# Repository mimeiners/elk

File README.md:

# HSB Fak. 4 ET B.Eng. M 5.3 Elektronik (ELK)

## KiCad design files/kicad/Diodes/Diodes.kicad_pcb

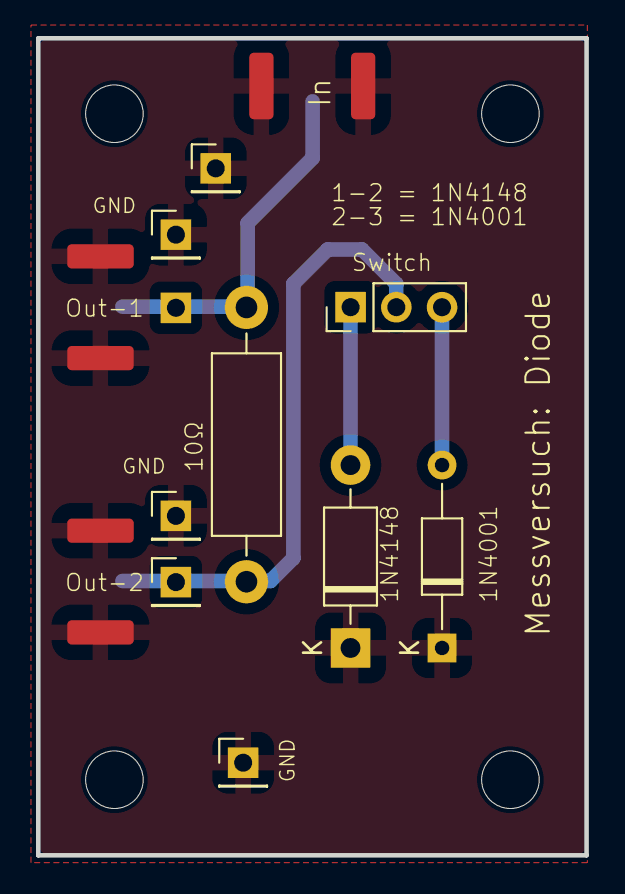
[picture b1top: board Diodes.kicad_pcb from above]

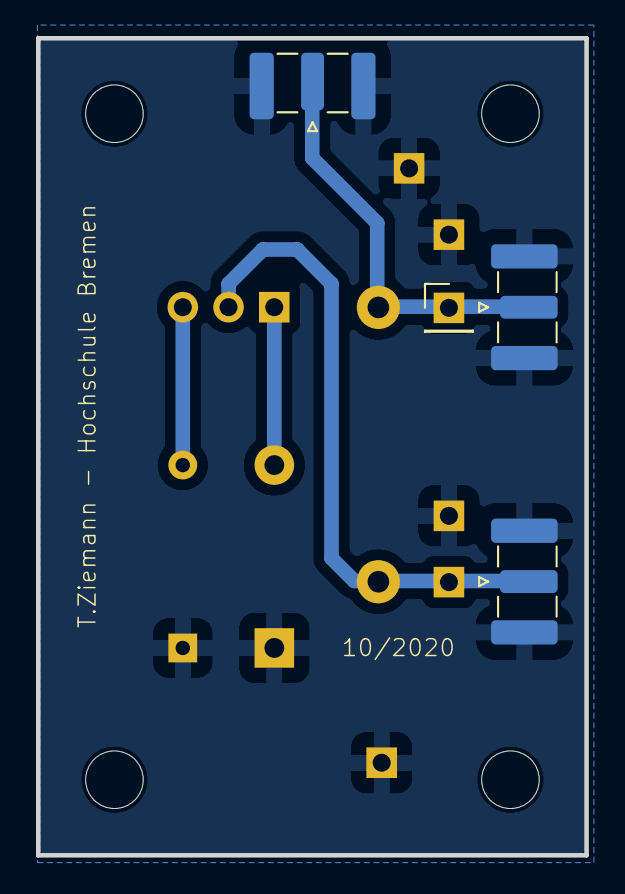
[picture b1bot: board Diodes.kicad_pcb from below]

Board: 2 copper layers, 30.5 x 45.4 mm, 17 parts (4 on the bottom side), 5 nets.

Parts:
D1: 1N4148; D_DO-35_SOD27_P10.16mm_Horizontal
D2: 1N4001; D_DO-41_SOD81_P10.16mm_Horizontal
GND1, GND2, GND3, GND4: Conn_01x01_Pin; PinHeader_1x01_P2.54mm_Vertical
H1, H2, H3, H4: MountingHole; MountingHole_3.2mm_M3
IN2: Conn_Coaxial; SMA_Samtec_SMA-J-P-H-ST-EM1_EdgeMount
Jumper1: Jumper_3_Bridged12; PinHeader_1x03_P2.54mm_Vertical
OUT-1, OUT-3: Conn_01x01_Pin; PinHeader_1x01_P2.54mm_Vertical
OUT-2, OUT-4: Conn_Coaxial; SMA_Samtec_SMA-J-P-H-ST-EM1_EdgeMount
R1: 10 Ohm; R_Axial_DIN0411_L9.9mm_D3.6mm_P15.24mm_Horizontal

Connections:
/In-1: IN2.1 (In), OUT-1.1, OUT-2.1 (In), R1.1
/Out-2: Jumper1.2 (C), OUT-3.1, OUT-4.1 (In), R1.2
GND: D1.1 (K), D2.1 (K), GND1.1, GND2.1, GND3.1, GND4.1, IN2.2 (Ext), OUT-2.2 (Ext), OUT-4.2 (Ext)
unnamed: D1.2 (A), Jumper1.3 (B)
unnamed: D2.2 (A), Jumper1.1 (A)

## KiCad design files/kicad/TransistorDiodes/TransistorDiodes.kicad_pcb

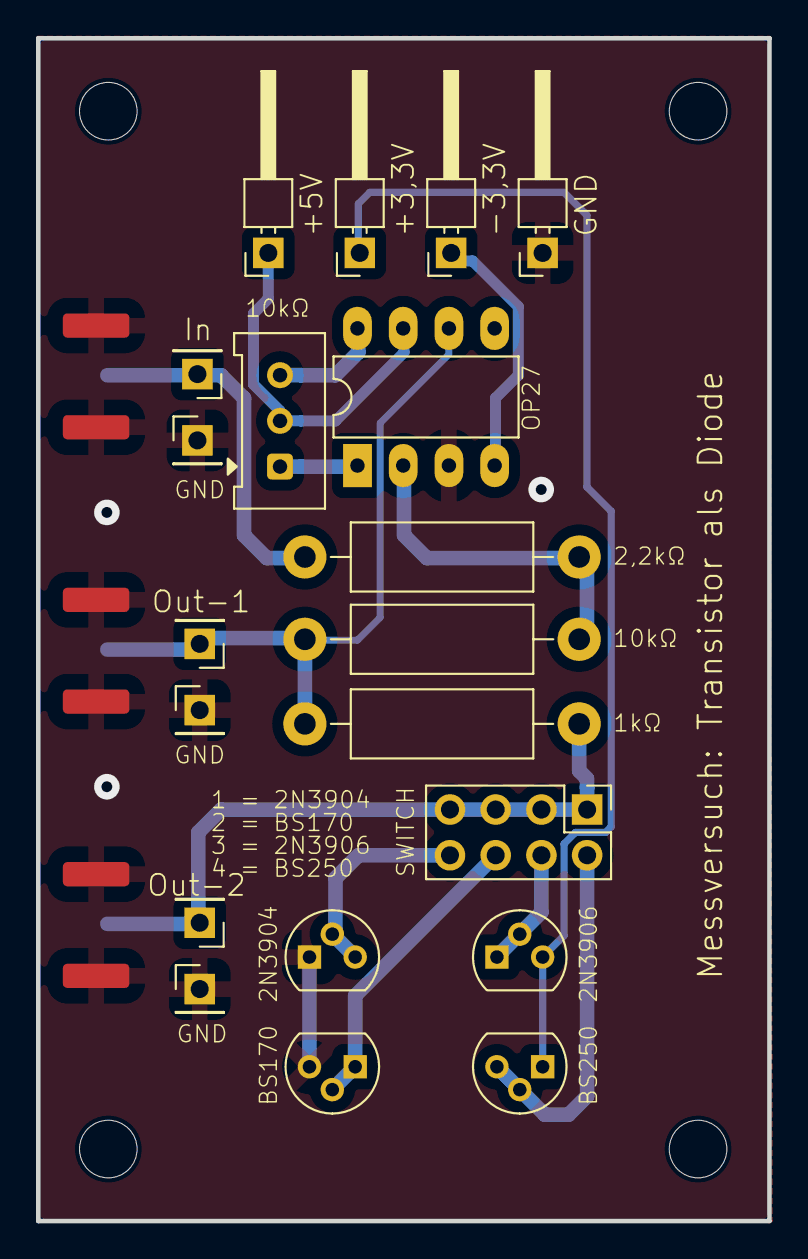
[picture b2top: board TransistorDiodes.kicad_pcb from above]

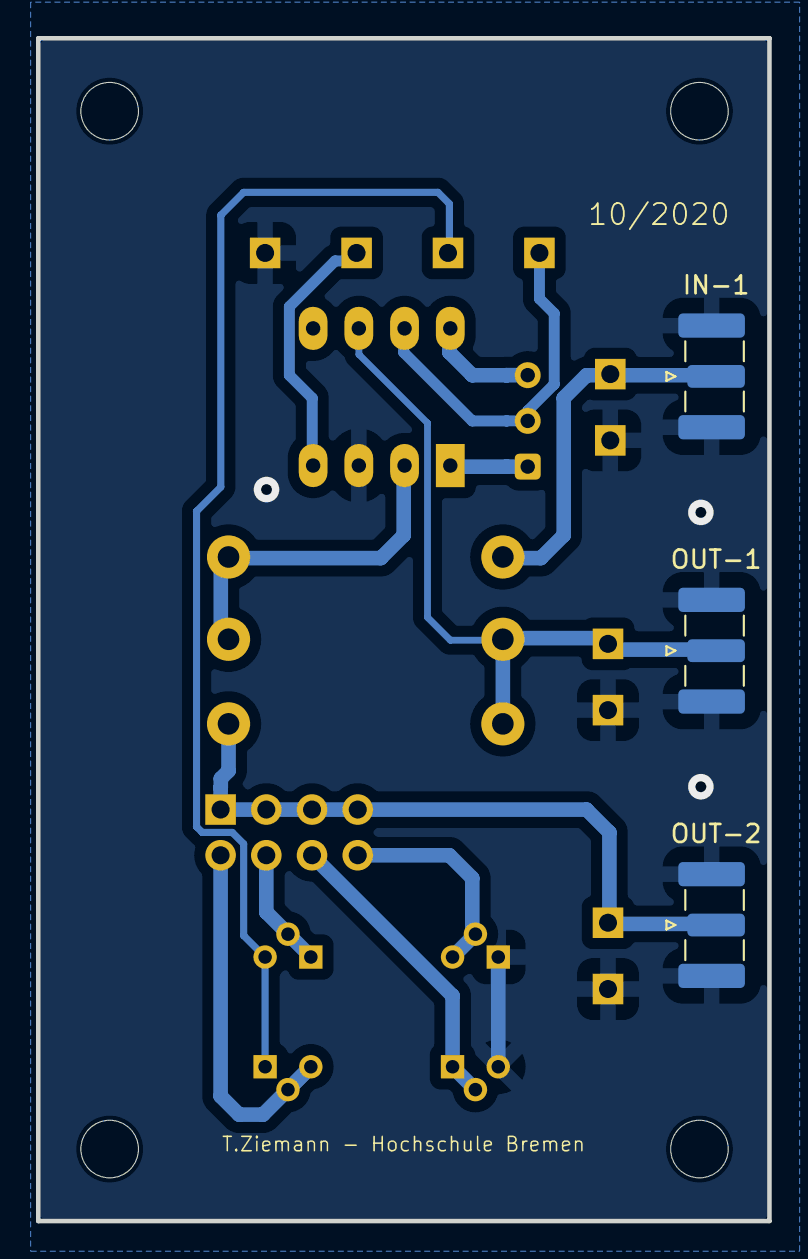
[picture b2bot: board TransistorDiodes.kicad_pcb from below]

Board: 2 copper layers, 40.6 x 65.7 mm, 27 parts (3 on the bottom side), 14 nets.

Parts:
+2: Conn_01x01_Pin; PinHeader_1x01_P2.54mm_Horizontal
-1: Conn_01x01_Pin; PinHeader_1x01_P2.54mm_Horizontal
GND1, GND2, GND3: Conn_01x01_Pin; PinHeader_1x01_P2.54mm_Vertical
H1, H2, H3, H4: MountingHole; MountingHole_3.2mm_M3
IN-1: Conn_Coaxial; SMA_Samtec_SMA-J-P-H-ST-EM1_EdgeMount
IN-2: Conn_01x01_Pin; PinHeader_1x01_P2.54mm_Vertical
J1: Conn_01x01_Pin; PinHeader_1x01_P2.54mm_Horizontal
JumperTransistorauswahl1: Conn_02x04_Odd_Even; PinHeader_2x04_P2.54mm_Vertical
OUT-1, OUT-2: Conn_Coaxial; SMA_Samtec_SMA-J-P-H-ST-EM1_EdgeMount
OUT-3, OUT-4: Conn_01x01_Pin; PinHeader_1x01_P2.54mm_Vertical
Q1: 2N3904; TO-92
Q2: 2N3906; TO-92
Q3: BS170; TO-92
Q4: BS250; TO-92
R1: 22k; R_Axial_DIN0411_L9.9mm_D3.6mm_P15.24mm_Horizontal
R2: 10k; R_Axial_DIN0411_L9.9mm_D3.6mm_P15.24mm_Horizontal
R3: 1k; R_Axial_DIN0411_L9.9mm_D3.6mm_P15.24mm_Horizontal
RV1: 10k; Potentiometer_Bourns_3386W_Horizontal
ST01: Conn_01x01_Pin; PinHeader_1x01_P2.54mm_Horizontal
U1: DIP-8_W7.62mm_LongPads

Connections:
+3V3: +2.1, Q2.3 (C), Q4.1 (D)
+5V: RV1.2, ST01.1, U1.7 (V+)
-3V3: -1.1, U1.4 (V-)
/2N3904: JumperTransistorauswahl1.8, Q1.2 (B), Q1.3 (C)
/2N3906: JumperTransistorauswahl1.6, Q3.1 (D), Q3.2 (G)
/BS170: JumperTransistorauswahl1.4, Q2.1 (E), Q2.2 (B)
/BS250: JumperTransistorauswahl1.2, Q4.2 (G), Q4.3 (S)
/IN-1: IN-1.1 (In), IN-2.1, R1.1
/OUT-1: OUT-1.1 (In), OUT-3.1, R2.2, R3.1, U1.6
/OUT-2: JumperTransistorauswahl1.1, JumperTransistorauswahl1.3, JumperTransistorauswahl1.5, JumperTransistorauswahl1.7, OUT-2.1 (In), OUT-4.1, R3.2
GND: GND1.1, GND2.1, GND3.1, IN-1.2 (Ext), J1.1, OUT-1.2 (Ext), OUT-2.2 (Ext), Q1.1 (E), Q3.3 (S), U1.3 (+)
unnamed: RV1.1, U1.1 (VOS)
unnamed: RV1.3, U1.8 (VOS)
unnamed: R1.2, R2.1, U1.2 (-)

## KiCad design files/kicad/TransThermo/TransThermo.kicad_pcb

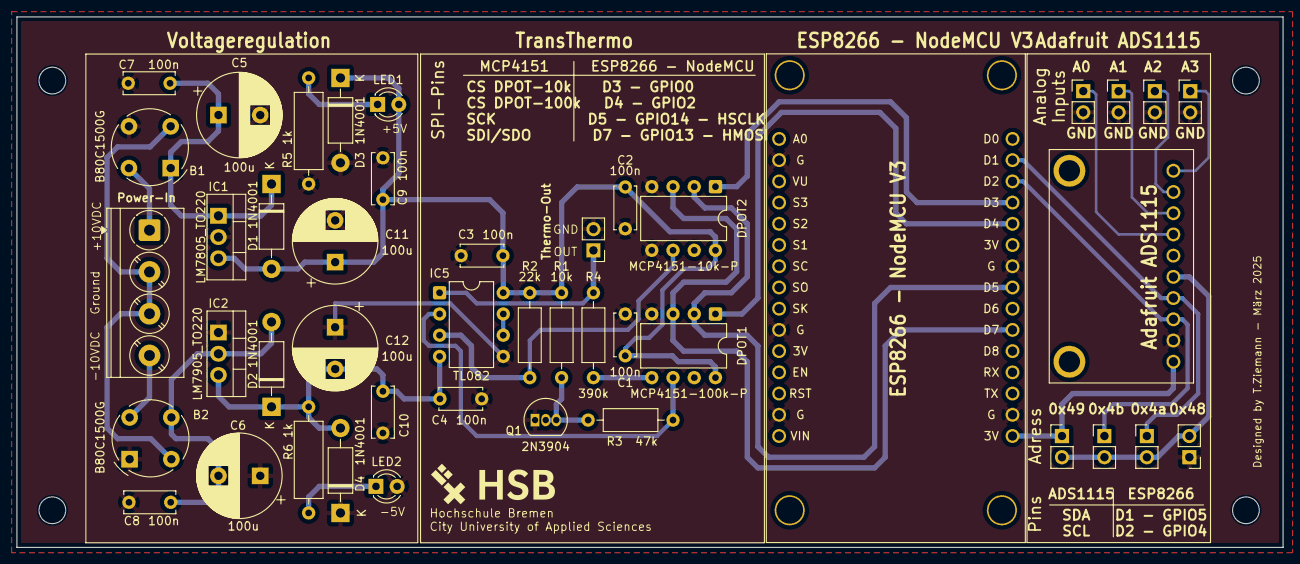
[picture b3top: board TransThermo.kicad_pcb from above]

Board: 2 copper layers, 151.6 x 63.5 mm, 49 parts (0 on the bottom side), 28 nets.

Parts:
B1, B2: B80C1500G; Diode_Bridge_Round_D9.0mm
C1, C2, C3, C4: 100n; C_Disc_D5.0mm_W2.5mm_P5.00mm
C5, C6, C11, C12: 100u; CP_Radial_D10.0mm_P5.00mm
C7, C8, C9, C10: 100n; C_Disc_D6.0mm_W2.5mm_P5.00mm
D1, D2, D3, D4: 1N4001; D_DO-41_SOD81_P10.16mm_Horizontal
DPOT1: MCP4151-100k-P; DIP-8_W7.62mm
DPOT2: MCP4151-10k-P; DIP-8_W7.62mm
G*: LOGO; HSB-Logo
H1, H2, H3, H4: MountingHole; MountingHole_3.2mm_M3
IC1: LM7805_TO220; TO-220-3_Vertical
IC2: LM7905_TO220; TO-220-3_Vertical
IC3: ESP8266 - NodeMCU V3; ESP8266-NodeMCU-V3
IC4: Adafruit-ADS1115
IC5: TL082; DIP-8_W7.62mm
J1: +/- Input (15V-25V); TerminalBlock_Phoenix_PT-1,5-4-5.0-H_1x04_P5.00mm_Horizontal
J2: Conn_01x02_Socket; PinHeader_1x02_P2.54mm_Vertical
JP1: Jumper_2_Bridged; PinHeader_1x02_P2.54mm_Vertical
JP2, JP3, JP4, JP5, JP6, JP7, JP8: Jumper_2_Open; PinHeader_1x02_P2.54mm_Vertical
LED1, LED2: LED; LED_D3.0mm
Q1: 2N3904; TO-92_Inline
R1: 10k; R_Axial_DIN0207_L6.3mm_D2.5mm_P10.16mm_Horizontal
R2: 22k; R_Axial_DIN0207_L6.3mm_D2.5mm_P10.16mm_Horizontal
R3: 47k; R_Axial_DIN0207_L6.3mm_D2.5mm_P10.16mm_Horizontal
R4: 390k; R_Axial_DIN0207_L6.3mm_D2.5mm_P10.16mm_Horizontal
R5, R6: 1k; R_Axial_DIN0309_L9.0mm_D3.2mm_P12.70mm_Horizontal

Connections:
0: B1.3 (-), B2.1 (+), C1.2, C2.2, C3.2, C4.1, C5.2, C6.1, C7.2, C8.1, C9.2, C10.1, C11.2, C12.1, D3.2 (A), D4.1 (K), DPOT1.4 (V_{SS}), DPOT2.4 (V_{SS}), DPOT2.5 (P0A), IC1.2 (GND), IC2.1 (GND), IC3.2 (G-GND), IC3.10 (G-GND), IC3.14 (G-GND), IC3.17 (G-GND), IC3.24 (G-GND), IC4.2 (GND), IC5.5 (+), J2.2, JP1.1 (A), JP5.2 (B), JP6.2 (B), JP7.2 (B), JP8.2 (B), LED2.2 (A), Q1.1 (E), R5.1
/+10V: B1.4, J1.1
/-10V: B2.4, J1.4
/CSP10k: DPOT2.1 (~CS), IC3.27 (D3-GPIO0-FLASH)
/CSP100k: DPOT1.1 (~CS), IC3.26 (D4-GPIO2-TXD1)
/Ground: B1.2, B2.2, J1.2, J1.3
/HMOSI: DPOT1.3 (SDI/SDO), DPOT2.3 (SDI/SDO), IC3.21 (D7-GPIO13-RXD2-HMOSI)
/HSCLK: DPOT1.2 (SCK), DPOT2.2 (SCK), IC3.23 (D5-GPIO14-HSCLK)
unnamed: B1.1 (+), C5.1, C7.1, D1.1 (K), IC1.1 (VI)
unnamed: B2.3 (-), C6.2, C8.2, D2.2 (A), IC2.2 (VI)
unnamed: DPOT1.5 (P0A), R4.1
unnamed: DPOT1.6 (P0W), IC5.2 (-), R3.2
unnamed: DPOT2.6 (P0W), IC5.3 (+), R2.2
unnamed: IC3.29 (D1-GPIO5), IC4.4 (SDA), JP4.1 (A)
unnamed: IC3.28 (D2-GPIO4), IC4.3 (SCL), JP3.1 (A)
unnamed: IC4.7 (A0), JP5.1 (A)
unnamed: IC4.8 (A1), JP6.1 (A)
unnamed: IC4.9 (A2), JP7.1 (A)
unnamed: IC4.10 (A3), JP8.1 (A)
unnamed: IC4.5 (ADDR), JP1.2 (B), JP2.2 (B), JP3.2 (B), JP4.2 (B)
unnamed: IC3.16 (3V-3.3V), IC4.1 (VDD), JP2.1 (A)
unnamed: IC5.6 (-), IC5.7
unnamed: IC5.1, J2.1, R4.2
unnamed: LED1.1 (K), R5.2
unnamed: LED2.1 (K), R6.2
unnamed: Q1.2 (B), Q1.3 (C), R1.2, R3.1
VCC: C1.1, C2.1, C3.1, C9.1, C11.1, D1.2 (A), D3.1 (K), DPOT1.8 (V_{DD}), DPOT2.8 (V_{DD}), IC1.3 (VO), IC5.8 (V+), LED1.2 (A), R1.1, R2.1
VEE: C4.2, C10.2, C12.2, D2.1 (K), D4.2 (A), IC2.3 (VO), IC5.4 (V-), R6.1

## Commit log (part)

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2022-09-27 Update documentation
2022-10-24 Reviewed class and lab
2022-10-24 Laborbeschreibung reviewed
2023-11-13 New class files
2023-12-14 erster Versuch
2023-12-14 neue Datei
2023-12-14 neue Spice-Datei
2024-01-30 Spice-daten
2024-01-30 neue Dateien
2024-02-09 Python-Code überarbeitet
2024-05-31 meine Änderung
2024-05-31 neues Skript
2024-06-25 neue Redpitayas Messwerte
2024-06-25 Review FlexiL Aufgabe
2024-10-16 Rework of ELK
2024-10-16 Intro ELK
2024-11-04 Quarto port init
2024-11-04 Built site for gh-pages
2024-11-04 Clean up
2024-11-04 Kleine Korrekturen, bib
2024-11-04 Kleine Korrekturen, Signale
2024-11-08 PDF ePub publish rework
2024-11-12 Added html ref
2024-11-12 Del ref html
2024-11-18 Re-order of lec
2024-11-20 Added pptx2md lectures signals, diodes
2024-11-22 pptx2md all lec-files and images added
2024-11-26 added new images physics lec-03
2024-12-09 Added lfs
2025-06-26 TranThermo added
2025-09-15 Umsortierung
2025-10-20 Fix image formatting in 02_Activity.qmd
2025-10-21 TranThermo fixed
2025-10-27 Added elk-proj data
2025-10-27 Updated lec-01
2025-10-27 Deleted ltspice2 files
2025-11-03 New lec-02
2025-11-04 SCPI scripts
2025-11-10 Added submodules for ADS1115 driver
2025-11-10 Re-ordered data
2025-11-10 Cleaned bib
2025-11-11 update redpitaya_scpi
2025-11-17 lec-03-diodes new
2025-11-18 New lec 01, 02, 03
2025-11-24 New _quarto.yml, book project
2025-12-02 DMM scripts
2025-12-05 STEMlab SCPI Korrekturen
2025-12-08 Spyder Project, SCPI timings test
2025-12-10 New hw and lec
2025-12-10 New lec_04
2025-12-12 Added kicad projects
2026-01-01 Final lectures and clean images
2026-01-05 Update lec and hw
2026-01-21 lec_06 update
2026-06-21 Moved to typst
